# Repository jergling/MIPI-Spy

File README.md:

# MIPI Spy
 Hardware tools for non-invasively sniffing MIPI D-Phy links. 

In order to contribute useful data to the OpenHD project, I designed a simple PCB that splices two 15-pin MIPI FFCs end-to-end, to allow non-invasive, man-in-the-middle sniffing of the data. This serves several purposes:

## Non-destructive and low-risk probing of the I2C bus
No more risk of shorting or ripping pads by clipping onto the FPC connector
## Latency benchmarking
Sensor ICs incorporate buffering stages between pixel capture and ISP. By probing the data lanes and a strobing light source, one can measure how long the module takes to process each pixel/line/stripe/field/frame as the delay between the strobe pulse and the first transmission of "bright" bytes on a data lane. This will help determine which modules are best suited to our low-latency application.
## Accurate probing of sLVDS
Due to the sensitivity of LVDS to impedence changes and phase, the length and impedence-matched routing on the MIPI Spy presents the best possible scenario for observing the signal with minimual harm to the transmission quality. Ideally, this means 0 extra retransmissions incurred due to instrumentation. Compared to scratching the coating off of an FFC and soldering on leads, this is a major step up.

# Hardware

## Pi version (v1.0)
- 15-FFC (1.0mm pitch) to 15-FFC (1.0mm pitch) F/F with 15-pin breakout header (2.54 mm pitch)
- Requires 15-wire MIPI camera, 2 flex cables (one top-bottom, one top-top), and a host machine with support for the camera module
- Awaiting validation samples

## DJI-A version (*not done*)
- Hirose DF56-26P to DF56-26P with 26-pin breakout header
- Requires 2 DJI or Caddx FPV camera cables, a DJI FPV compatible camera, and a DJI or compatible air unit
- May not be possible due to unavailability of DF56-26S connectors

## DJI-B version (*not done*)
- Hirose DF36-30P to DF36-30P with 30-pin breakout header
- Requires 2 custom DF56-to-DF36 cables, a DJI FPV compatible camera, and a DJI or compatible air unit
- Alternative to DJI-A in case of sourcing issues
- Higher cost due to custom cable requirement

## HDZero Version (*not done*)
- Hirose DF36-20P to DF36-20P with 20-pin breakout header
- Requires 2 HDzero "Mipi" cables, an HDZero camera, and an HDZero VTX
- According to sources, this is actually a DVP link, not MIPI

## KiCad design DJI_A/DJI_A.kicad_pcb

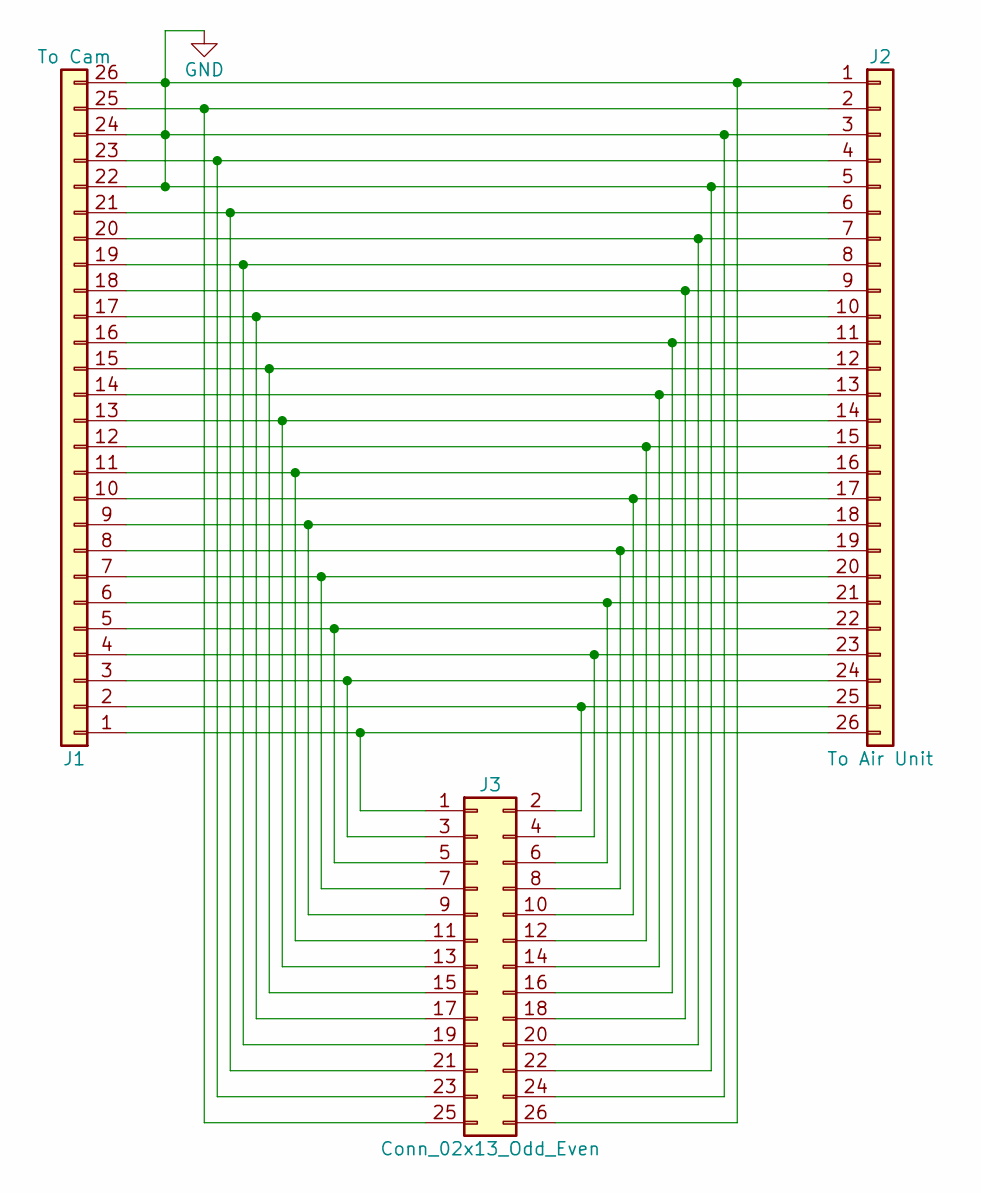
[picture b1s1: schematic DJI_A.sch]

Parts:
J1: To Cam; DF56C-26S
J2: To Air Unit; DF56C-26S
J3: Conn_02x13_Odd_Even; PinHeader_2x13_P2.54mm_Vertical

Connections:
GND: J1.22, J1.24, J1.26, J1.GND, J2.1, J2.3, J2.5, J2.GND, J3.22, J3.24, J3.26
unnamed: J1.1, J2.26, J3.1
unnamed: J1.2, J2.25, J3.2
unnamed: J1.3, J2.24, J3.3
unnamed: J1.4, J2.23, J3.4
unnamed: J1.5, J2.22, J3.5
unnamed: J1.6, J2.21, J3.6
unnamed: J1.7, J2.20, J3.7
unnamed: J1.8, J2.19, J3.8
unnamed: J1.9, J2.18, J3.9
unnamed: J1.10, J2.17, J3.10
unnamed: J1.11, J2.16, J3.11
unnamed: J1.12, J2.15, J3.12
unnamed: J1.13, J2.14, J3.13
unnamed: J1.14, J2.13, J3.14
unnamed: J1.15, J2.12, J3.15
unnamed: J1.16, J2.11, J3.16
unnamed: J1.17, J2.10, J3.17
unnamed: J1.18, J2.9, J3.18
unnamed: J1.19, J2.8, J3.19
unnamed: J1.20, J2.7, J3.20
unnamed: J1.21, J2.6, J3.21
unnamed: J1.23, J2.4, J3.23
unnamed: J1.25, J2.2, J3.25

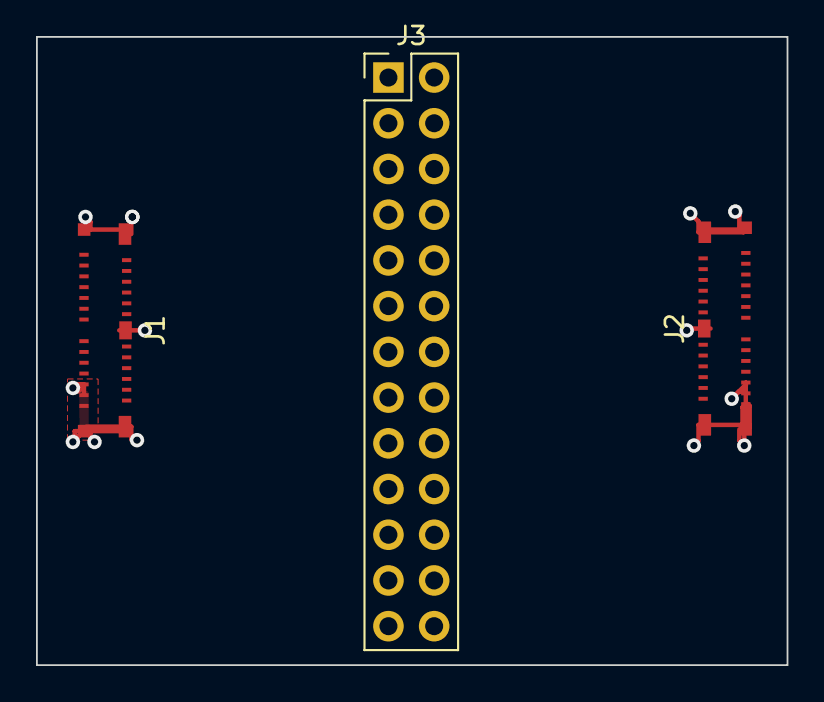
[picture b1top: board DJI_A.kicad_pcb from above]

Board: 2 copper layers, 41.7 x 34.9 mm, 3 parts (0 on the bottom side), 24 nets.

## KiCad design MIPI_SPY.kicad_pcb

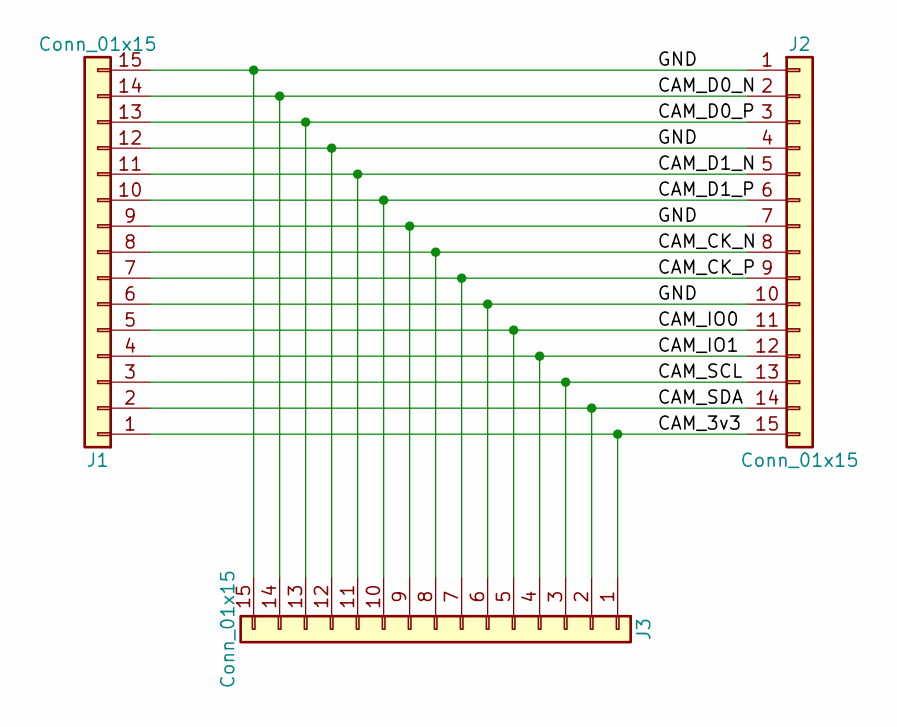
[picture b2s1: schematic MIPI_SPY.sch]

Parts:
J1, J2: Conn_01x15; TE_1-84952-5_1x15-1MP_P1.0mm_Horizontal
J3: Conn_01x15; PinHeader_1x15_P2.54mm_Vertical

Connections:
/CAM_3v3: J1.1, J2.15, J3.1
/CAM_CK_N: J1.8, J2.8, J3.8
/CAM_CK_P: J1.7, J2.9, J3.7
/CAM_D0_N: J1.14, J2.2, J3.14
/CAM_D0_P: J1.13, J2.3, J3.13
/CAM_D1_N: J1.11, J2.5, J3.11
/CAM_D1_P: J1.10, J2.6, J3.10
/CAM_IO0: J1.5, J2.11, J3.5
/CAM_IO1: J1.4, J2.12, J3.4
/CAM_SCL: J1.3, J2.13, J3.3
/CAM_SDA: J1.2, J2.14, J3.2
/GND: J1.6, J1.9, J1.12, J1.15, J2.1, J2.4, J2.7, J2.10, J3.6, J3.9, J3.12, J3.15

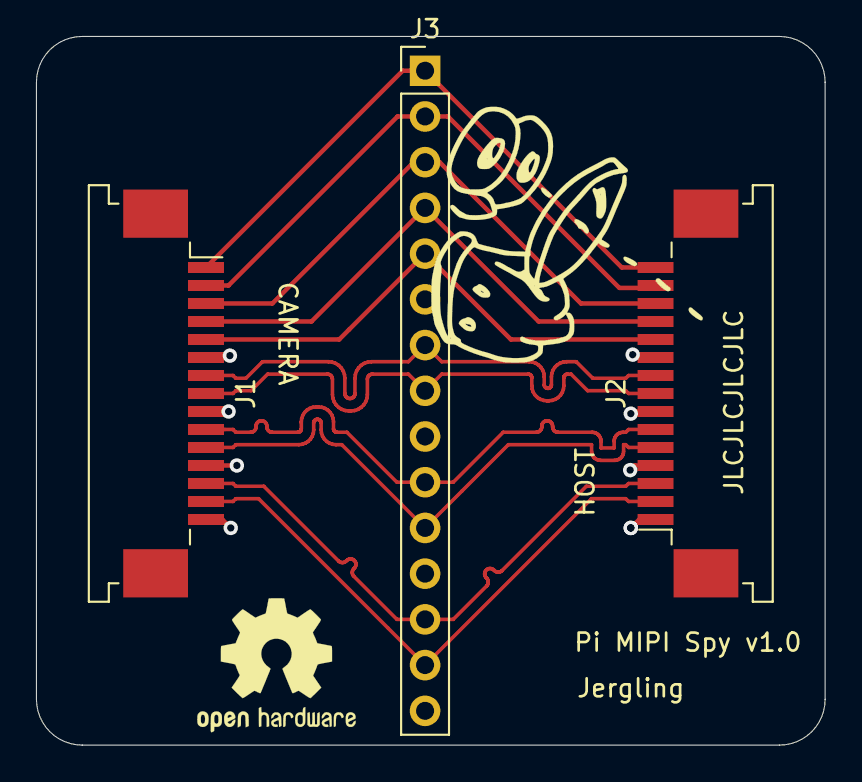
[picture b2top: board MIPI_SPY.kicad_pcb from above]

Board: 2 copper layers, 43.8 x 39.4 mm, 3 parts (0 on the bottom side), 12 nets.

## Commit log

2022-01-07 Initial Commit
    Committing all ECAD for the v1.0 to the repo.
2022-01-07 Added image of board
2022-01-08 Subdivided by target, added DJI_A dir
2022-01-08 Unrouted DJI_A PCB added
2022-01-08 Possible straight-through pinout. Don't use this version.
